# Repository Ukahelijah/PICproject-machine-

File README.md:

this project is a embedded system hardware project 
it contain both the hardware design file an software

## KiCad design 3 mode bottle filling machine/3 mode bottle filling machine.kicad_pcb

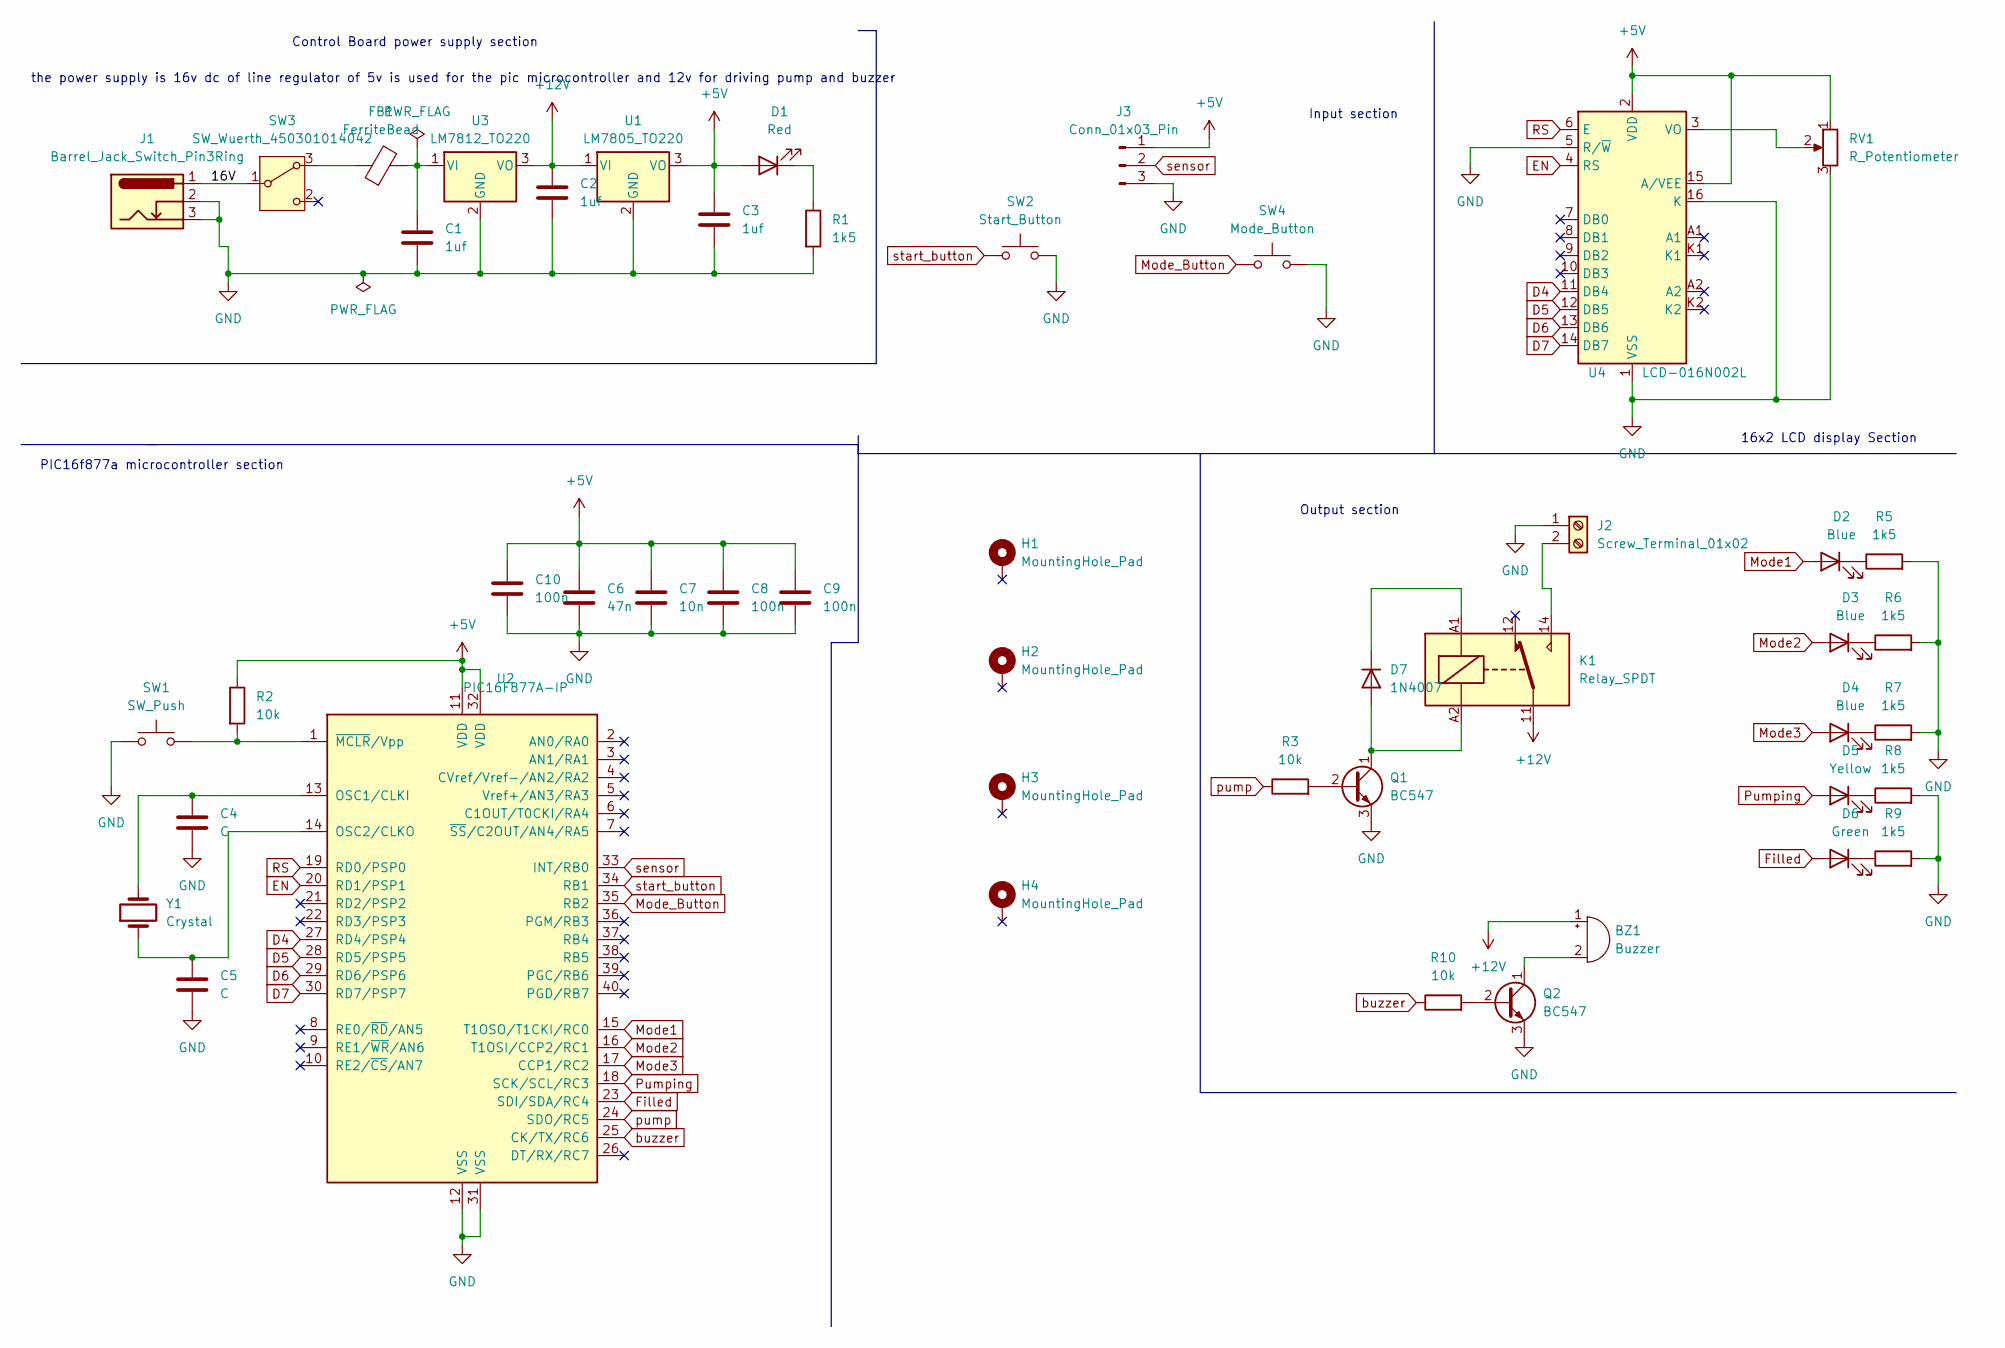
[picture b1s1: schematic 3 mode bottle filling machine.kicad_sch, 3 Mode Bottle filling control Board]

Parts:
BZ1: Buzzer; Buzzer_12x9.5RM7.6
C1, C2, C3: 1uf; C_Disc_D3.0mm_W1.6mm_P2.50mm
C4, C5: C; C_Disc_D3.0mm_W1.6mm_P2.50mm
C6: 47n; C_Disc_D3.0mm_W1.6mm_P2.50mm
C7: 10n; C_Disc_D3.0mm_W1.6mm_P2.50mm
C8, C9, C10: 100n; C_Disc_D3.0mm_W1.6mm_P2.50mm
D1: Red; LED_D3.0mm
D2, D3, D4: Blue; LED_D3.0mm
D5: Yellow; LED_D3.0mm
D6: Green; LED_D3.0mm
D7: 1N4007; D_DO-41_SOD81_P10.16mm_Horizontal
FB1: FerriteBead; L_0603_1608Metric
H1, H2, H3, H4: MountingHole_Pad; MountingHole_3mm_Pad_TopBottom
J1: Barrel_Jack_Switch_Pin3Ring; BarrelJack_Horizontal
J2: Screw_Terminal_01x02; TerminalBlock_bornier-2_P5.08mm
J3: Conn_01x03_Pin; SolderWire-0.75sqmm_1x03_P4.8mm_D1.25mm_OD2.3mm
K1: Relay_SPDT; Relay_SPDT_Finder_36.11
Q1, Q2: BC547; TO-92_Inline
R1, R5, R6, R7, R8, R9: 1k5; R_Axial_DIN0204_L3.6mm_D1.6mm_P5.08mm_Horizontal
R2, R3, R10: 10k; R_Axial_DIN0204_L3.6mm_D1.6mm_P5.08mm_Horizontal
RV1: R_Potentiometer; Potentiometer_Vishay_T73YP_Vertical
SW1: SW_Push; SW_Tactile_Straight_KSL0Axx1LFTR
SW2: Start_Button; SW_PUSH-12mm
SW3: SW_Wuerth_450301014042; SW_Slide-03_Wuerth-WS-SLTV_10x2.5x6.4_P2.54mm
SW4: Mode_Button; SW_PUSH-12mm
U1: LM7805_TO220; TO-220-3_Vertical
U2: PIC16F877A-IP; DIP-40_W15.24mm_LongPads
U3: LM7812_TO220; TO-220-3_Vertical
U4: LCD-016N002L
Y1: Crystal; Crystal_HC52-U_Vertical

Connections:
+5V: C3.1, C6.1, C7.1, C8.1, C9.1, C10.1, D1.2 (A), J3.1, R2.1, RV1.1, U1.3 (VO), U2.11 (VDD), U2.32 (VDD), U4.2 (VDD), U4.15 (A/VEE)
+12V: BZ1.1 (+), C2.1, K1.11, U1.1 (VI), U3.3 (VO)
/16V: J1.1, SW3.1 (B)
D4: U2.27 (RD4/PSP4), U4.11 (DB4)
D5: U2.28 (RD5/PSP5), U4.12 (DB5)
D6: U2.29 (RD6/PSP6), U4.13 (DB6)
D7: U2.30 (RD7/PSP7), U4.14 (DB7)
EN: U2.20 (RD1/PSP1), U4.4 (RS)
Filled: D6.2 (A), U2.23 (SDI/SDA/RC4)
GND: C1.2, C2.2, C3.2, C4.2, C5.2, C6.2, C7.2, C8.2, C9.2, C10.2, J1.2, J1.3, J2.1, J3.3, Q1.3 (E), Q2.3 (E), R1.2, R5.2, R6.2, R7.2, R8.2, R9.2, RV1.3, SW1.1, SW2.2, SW4.2, U1.2 (GND), U2.12 (VSS), U2.31 (VSS), U3.2 (GND), U4.1 (VSS), U4.5 (R/~W), U4.16 (K)
Mode1: D2.2 (A), U2.15 (T1OSO/T1CKI/RC0)
Mode2: D3.2 (A), U2.16 (T1OSI/CCP2/RC1)
Mode3: D4.2 (A), U2.17 (CCP1/RC2)
Mode_Button: SW4.1, U2.35 (RB2)
unnamed: BZ1.2 (-), Q2.1 (C)
unnamed: D1.1 (K), R1.1
unnamed: D2.1 (K), R5.1
unnamed: D3.1 (K), R6.1
unnamed: D4.1 (K), R7.1
unnamed: D5.1 (K), R8.1
unnamed: D6.1 (K), R9.1
unnamed: D7.2 (A), K1.A2, Q1.1 (C)
unnamed: D7.1 (K), K1.A1
unnamed: J2.2, K1.14
unnamed: Q1.2 (B), R3.2
unnamed: Q2.2 (B), R10.2
unnamed: FB1.1, SW3.3 (A)
unnamed: C4.1, U2.13 (OSC1/CLKI), Y1.2
unnamed: C5.1, U2.14 (OSC2/CLKO), Y1.1
unnamed: R2.2, SW1.2, U2.1 (~MCLR/Vpp)
unnamed: C1.1, FB1.2, U3.1 (VI)
unnamed: RV1.2, U4.3 (VO)
Pumping: D5.2 (A), U2.18 (SCK/SCL/RC3)
RS: U2.19 (RD0/PSP0), U4.6 (E)
buzzer: R10.1, U2.25 (CK/TX/RC6)
pump: R3.1, U2.24 (SDO/RC5)
sensor: J3.2, U2.33 (INT/RB0)
start_button: SW2.1, U2.34 (RB1)

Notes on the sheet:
the power supply is 16v dc of line regulator of 5v is used for the pic microcontroller and 12v for driving pump and buzzer
16x2 LCD display Section
Output section
PIC16f877a microcontroller section
Input section
Control Board power supply section

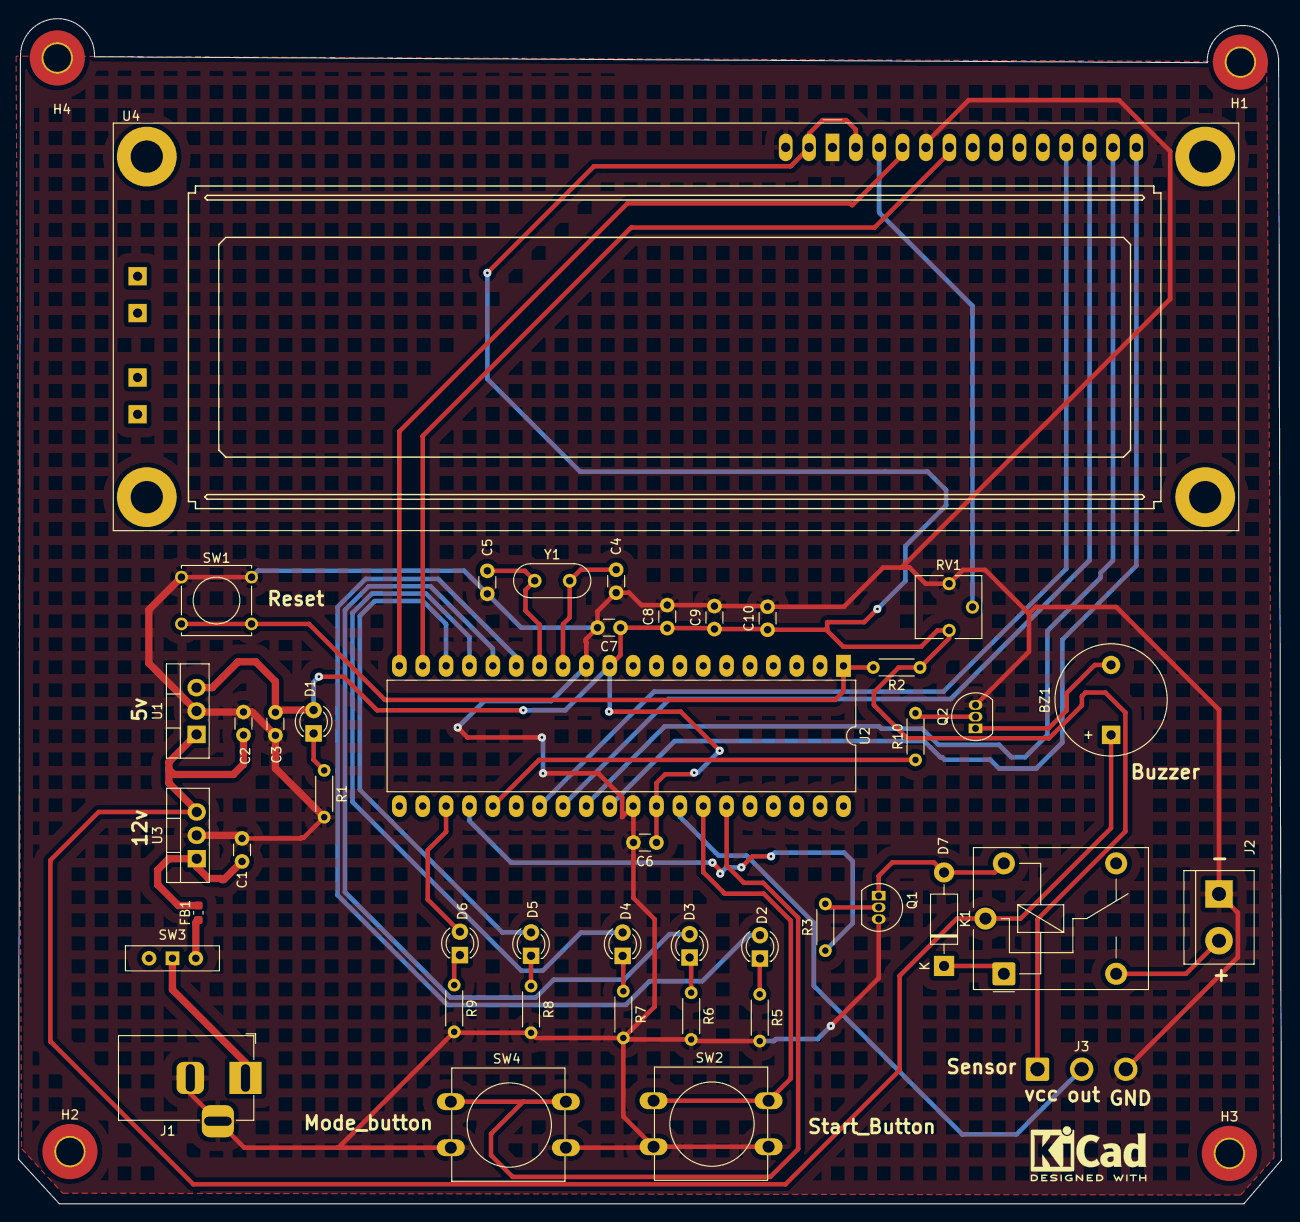
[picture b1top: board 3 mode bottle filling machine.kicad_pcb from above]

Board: 2 copper layers, 137.2 x 128.8 mm, 48 parts (0 on the bottom side), 38 nets.

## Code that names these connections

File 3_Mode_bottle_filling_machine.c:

// PIC16F877A Configuration Bit Settings

// 'C' source line config statements

// CONFIG
#pragma config FOSC = HS        // Oscillator Selection bits (HS oscillator)
#pragma config WDTE = OFF       // Watchdog Timer Enable bit (WDT disabled)
#pragma config PWRTE = OFF      // Power-up Timer Enable bit (PWRT disabled)
#pragma config BOREN = ON       // Brown-out Reset Enable bit (BOR enabled)
#pragma config LVP = OFF        // Low-Voltage (Single-Supply) In-Circuit Serial Programming Enable bit (RB3 is digital I/O, HV on MCLR must be used for programming)
#pragma config CPD = OFF        // Data EEPROM Memory Code Protection bit (Data EEPROM code protection off)
#pragma config WRT = OFF        // Flash Program Memory Write Enable bits (Write protection off; all program memory may be written to by EECON control)
#pragma config CP = OFF         // Flash Program Memory Code Protection bit (Code protection off)

// #pragma config statements should ` project file includes.
// Use project enums instead of #define for ON and OFF.

#include <xc.h>


#define _XTAL_FREQ 20000000
#define RS RC3
#define EN RC5
#define D4 RD4
#define D5 RD5
#define D6 RD6 
#define D7 RD7
#define StartButton RB1
#define ModeButton RB2
#define Bcheck RB0
#define Mode1 RC0
#define Mode2 RC1
#define Mode3 RC2
#define power RD1
#define pumping RC4
#define filled RD0
#define buzzer RC6
#define pump  RC7

int ChangeMode;




void LCD_SetBit(char data_bit){
    if(data_bit& 1)
        D4=1;
    else
        D4=0;
     if(data_bit& 2)
        D5=1;
    else
        D5=0;
     if(data_bit& 4)
        D6=1;
    else
        D6=0;
     if(data_bit& 8)
        D7=1;
    else
        D7=0;
}
void LCD_Cmd (char a){
   RS=0;
   LCD_SetBit(a);
   EN=1;
   __delay_ms(4);
   EN=0;
   
}
void LCD_Clear(){
    LCD_Cmd (0);
    LCD_Cmd (1);
}
void LCD_Start(){
    LCD_SetBit(0x00);
    for(int i=1065244; i<=0; i--)NOP();
    LCD_Cmd(0x03);
    __delay_ms(5);
     LCD_Cmd(0x03);
    __delay_ms(11);
     LCD_Cmd(0x03);
      LCD_Cmd(0x02);
       LCD_Cmd(0x02);
        LCD_Cmd(0x08);
         LCD_Cmd(0x00);
          LCD_Cmd(0x0C);
           LCD_Cmd(0x00);
            LCD_Cmd(0x06);
            
    
    
}

void LCD_Set_Cursor(char a, char b){
    char temp,z,y;
    if(a==1){
        temp= 0x80 + b - 1;
        z= temp>>4;
        y= temp & 0x0F;
        LCD_Cmd (z); 
         LCD_Cmd (y);
    }
    else if(a==2){
        temp= 0xC0 + b - 1;
        z= temp>>4;
        y= temp & 0x0F;
        LCD_Cmd (z); 
         LCD_Cmd (y);
    }
    
}
void LCD_Print_Char(char data){
    char Lower_Nibble,Upper_Nibble;
    Lower_Nibble = data & 0x0F;
    Upper_Nibble = data & 0xF0;
    RS=1;
    LCD_SetBit(Upper_Nibble>>4);
    EN=1;
    for(int i=2130483; i<=0; i--)NOP();
    EN=0;
    LCD_SetBit(Lower_Nibble);
    EN=1;
    for(int i=2130483; i<=0; i--)NOP();
    EN=0;
    
}
   
void LCD_Print_String(char *a){
    int i;
    for(i=0; a[i]!='\0'; i++)
        LCD_Print_Char(a[i]);
}

void beep(int c){
    for(int b=0; b<c; b++){
        buzzer=1;
         __delay_ms(50);
         buzzer=0;
          __delay_ms(50);
    }
}

void main(){
    TRISD=0x00;
    TRISC=0x00;
    TRISB=1;
    //PORTB=1;
   unsigned int a;
   
   StartButton=1;
   ModeButton=1;
    power=1;
    ChangeMode=1;
    pump=0;
    pumping=0;
    filled=0;
     LCD_Start();
    LCD_Clear();
    LCD_Set_Cursor(1,1);
    LCD_Print_String("Welcome to NCAT");
    LCD_Set_Cursor(2,1);
    LCD_Print_String("  MTCE Workshop");
    __delay_ms(200);
    LCD_Clear();
    LCD_Set_Cursor(1,1);
    LCD_Print_String("     3 MODE     ");
    LCD_Set_Cursor(2,1);
    LCD_Print_String(" Bottle Filling ");
    __delay_ms(200);
    LCD_Clear();
    LCD_Set_Cursor(1,1);
    LCD_Print_String("     Machine     ");
    LCD_Set_Cursor(2,1);
    LCD_Print_String("  Starting");
    __delay_ms(250);
    LCD_Set_Cursor(2,11);
    LCD_Print_String(".");
     __delay_ms(250);
    LCD_Set_Cursor(2,12);
    LCD_Print_String(".");
     __delay_ms(250);
    LCD_Set_Cursor(2,13);
    LCD_Print_String(".");
     __delay_ms(250);
    LCD_Set_Cursor(2,14);
    LCD_Print_String(".");
    beep(1);
    LCD_Clear();
    
    while(1){
        while(StartButton==1){
           LCD_Set_Cursor(2,1);
    LCD_Print_String("  Place Bottle  ");
    break;
    
        }
        filled=0;
        if(StartButton==0 && Bcheck==0){
            LCD_Set_Cursor(2,1);
            LCD_Print_String("Error! No Bottle");
            beep(3);
            __delay_ms(200);
        }
          while(Bcheck==1){
           LCD_Set_Cursor(2,1);
    LCD_Print_String("   Push Start   "); 
    if(StartButton==0 && ChangeMode==1 && Bcheck==1){
        __delay_ms(200);
        beep(2);
        LCD_Set_Cursor(2,1);
    LCD_Print_String("   Filling...   "); 
             pump=1;
             pumping=1;
             __delay_ms(3000);
             pump=0;
             pumping=0;
             __delay_ms(200);
             filled=1;
             
            
             LCD_Set_Cursor(2,1);
    LCD_Print_String("   Completed    ");
             while(Bcheck=1){
                 if(StartButton==0){
                     LCD_Set_Cursor(2,1);
    LCD_Print_String("Place New Bottle");
    beep(3);
    __delay_ms(200);
    LCD_Set_Cursor(2,1);
    LCD_Print_String("   Completed    "); 
    StartButton=1;
                 }
             }
        
    }
      if(StartButton==0 && ChangeMode==2 && Bcheck==1){
        __delay_ms(200);
        beep(2);
        LCD_Set_Cursor(2,1);
    LCD_Print_String("   Filling...   "); 
             pump=1;
             pumping=1;
             __delay_ms(2000);
             pump=0;
             pumping=0;
             __delay_ms(1000);
             filled=1;
             LCD_Set_Cursor(2,1);
    LCD_Print_String("   Completed    ");
             while(Bcheck=1){
                 if(StartButton==0){
                     LCD_Set_Cursor(2,1);
    LCD_Print_String("Place New Bottle");
    __delay_ms(200);
    beep(3);
    LCD_Set_Cursor(2,1);
    LCD_Print_String("   Completed    "); 
    StartButton=1;
                 }
             }
        
    }
      if(StartButton==0 && ChangeMode==3 && Bcheck==1){
        __delay_ms(200);
        beep(2);
        LCD_Set_Cursor(2,1);
    LCD_Print_String("   Filling...   "); 
             pump=1;
             pumping=1;
             __delay_ms(3000);
             pump=0;
             pumping=0;
             __delay_ms(1000);
             filled=1;
             LCD_Set_Cursor(2,1);
    LCD_Print_String("   Completed    ");
             while(Bcheck=1){
                 if(StartButton==0){
                     LCD_Set_Cursor(2,1);
    LCD_Print_String("Place New Bottle");
    __delay_ms(200);
    beep(3);
    LCD_Set_Cursor(2,1);
    LCD_Print_String("   Completed    "); 
    StartButton=1;
                 }
             }
        
    }
    
        }
        if(ModeButton==0){
            
            ChangeMode=ChangeMode+1;
            beep(1);
             
            
        }
        
        if(ChangeMode==1){
            Mode1=1;
            Mode2=0;
            Mode3=0;
            LCD_Set_Cursor(1,1);
            LCD_Print_String(" MODE 1 = 250ml ");
        }
         if(ChangeMode==2){
            Mode1=0;
            Mode2=1;
            Mode3=0;
            
            LCD_Set_Cursor(1,1);
            LCD_Print_String(" MODE 2 = 350ml ");
        }
        if(ChangeMode==3){
            Mode1=0;
            Mode2=0;
            Mode3=1;
            
            LCD_Set_Cursor(1,1);
            LCD_Print_String(" MODE 3 = 500ml ");
        }
        if(ChangeMode>=4){
            ChangeMode=1;
        }

    }
}

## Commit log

2024-07-31 First
